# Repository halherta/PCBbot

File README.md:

# Introducing PCBbot!

The PCBBot leverages the PCB itself as the chassis. This reduces cost significantly. It also means that the two motors and the caster wheel would have to be mounted on the PCB itself, in addition to the batteries and all the other components...

For more info have a look at the write up on my [blog entry](https://hussamtalkstech.com/introducing-pcbbot/)

In this Github repo, you'll find my PCBBot KiCAD PCB design freely available (MIT License) along with a Digikey bill of materials (BOM) (caster wheel, motor brackets and motors not included) and MicroPython code. I’m also providing my [custom symbol and footprint libraries in this repo](https://github.com/halherta/mykicadlibrary). Feel free to make your own version of the PCBBot as is or modify it to suit your needs. Have fun!

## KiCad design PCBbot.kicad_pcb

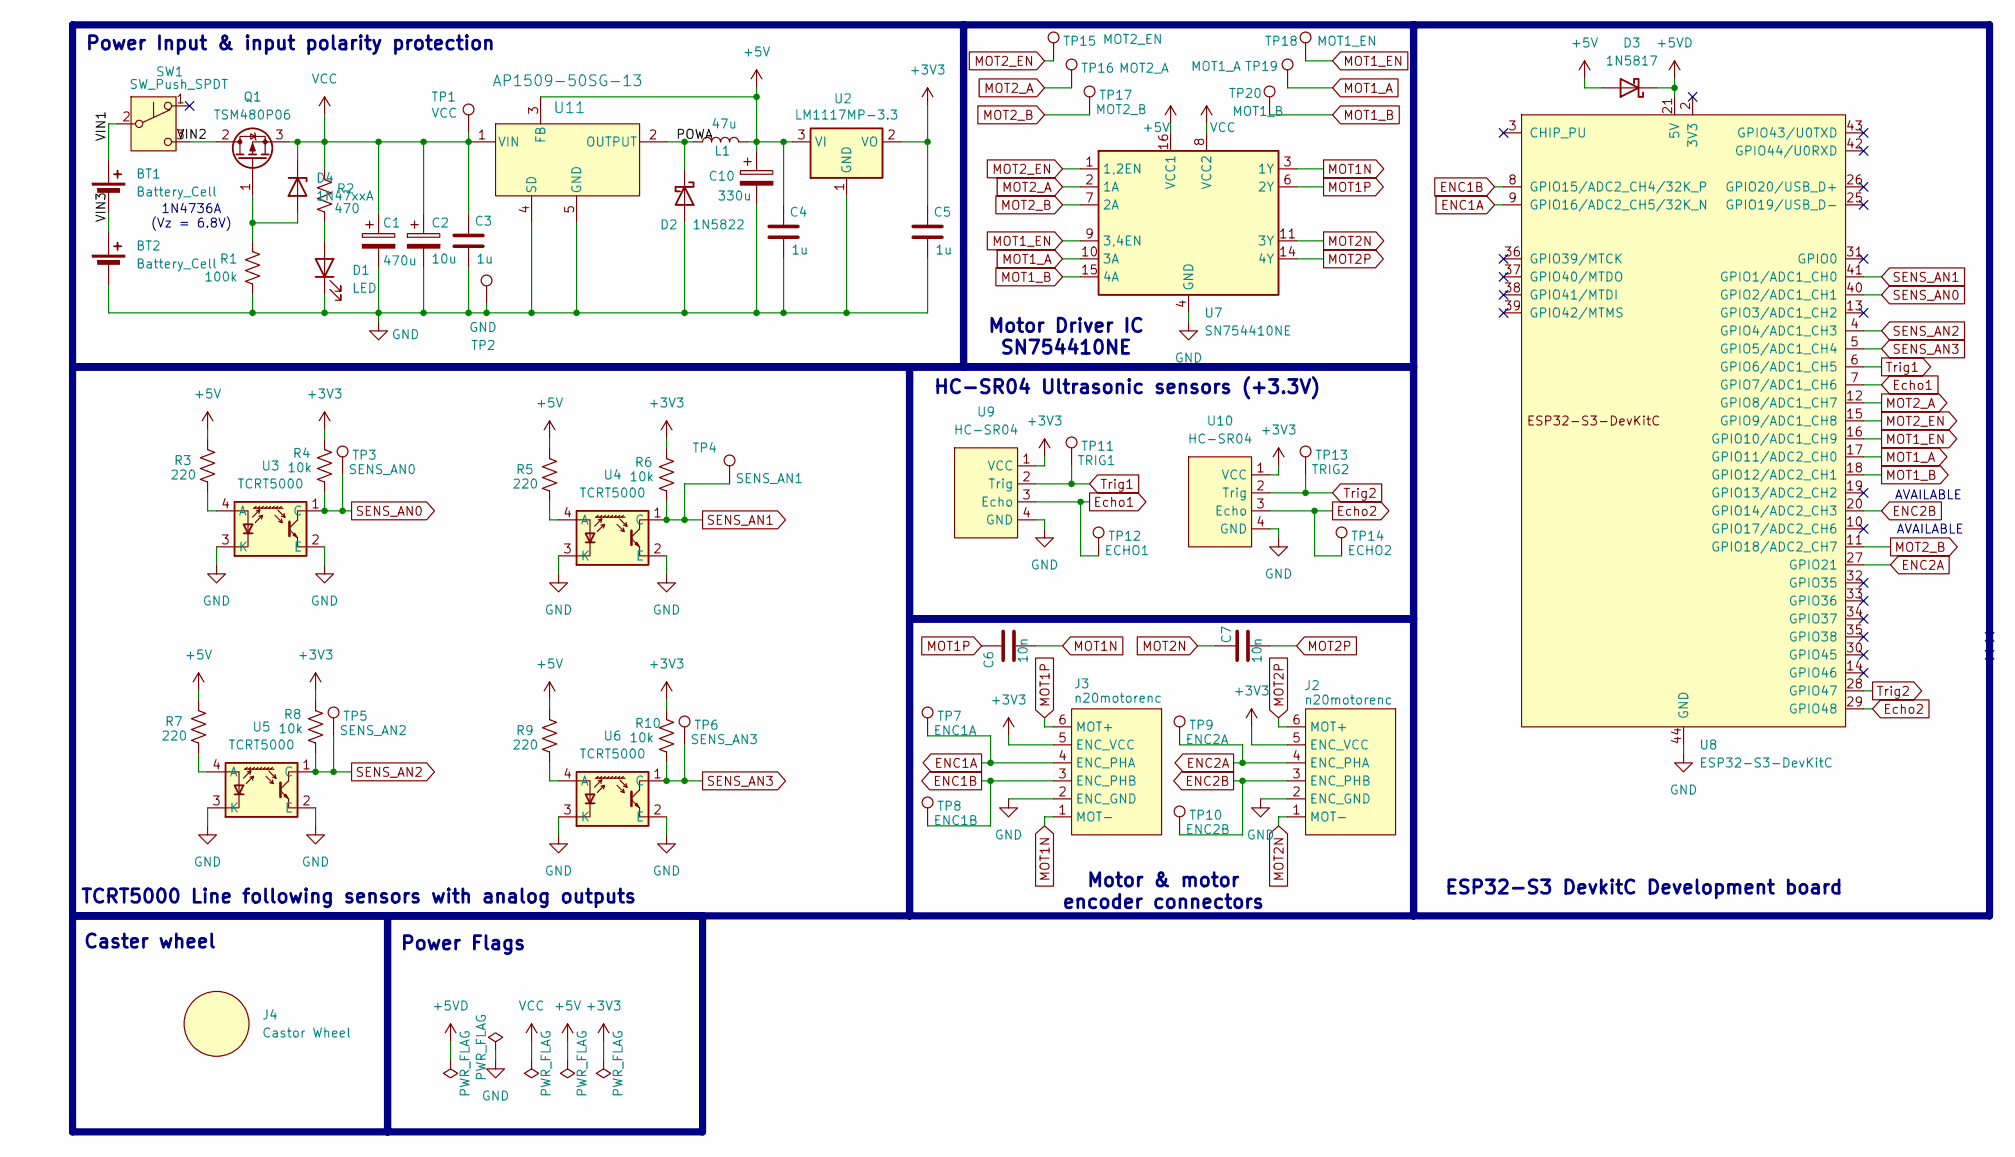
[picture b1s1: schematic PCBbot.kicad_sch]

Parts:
BT1, BT2: Battery_Cell; BatteryHolder_MPD_BK-18650-PC2
C1: 470u; CP_Radial_D10.0mm_P5.00mm
C2: 10u; CP_Radial_D5.0mm_P2.50mm
C3, C4, C5: 1u; C_Disc_D4.3mm_W1.9mm_P5.00mm
C6, C7: 10n; C_Disc_D4.3mm_W1.9mm_P5.00mm
C10: 330u; CP_Radial_D10.0mm_P5.00mm
D1: LED; LED_D5.0mm
D2: 1N5822; D_DO-201AD_P15.24mm_Horizontal
D3: 1N5817; D_DO-41_SOD81_P10.16mm_Horizontal
D4: 1N47xxA; D_DO-41_SOD81_P10.16mm_Horizontal
J2, J3: n20motorenc; n20motorencv2
J4: Castor Wheel; N20CasterSteelBall-Mini
L1: 47u; AIUR-06_ABRv2
Q1: TSM480P06; TO-251-3_Vertical
R1: 100k; R_Axial_DIN0207_L6.3mm_D2.5mm_P10.16mm_Horizontal
R2: 470; R_Axial_DIN0207_L6.3mm_D2.5mm_P10.16mm_Horizontal
R3, R5, R7, R9: 220; R_Axial_DIN0207_L6.3mm_D2.5mm_P10.16mm_Horizontal
R4, R6, R8, R10: 10k; R_Axial_DIN0207_L6.3mm_D2.5mm_P10.16mm_Horizontal
SW1: SW_Push_SPDT; SW_E-Switch_EG1224_SPDT_Angled
TP1: VCC; TestPoint_THTPad_D1.5mm_Drill0.7mm
TP2: GND; TestPoint_THTPad_D1.5mm_Drill0.7mm
TP3: SENS_AN0; TestPoint_THTPad_D1.5mm_Drill0.7mm
TP4: SENS_AN1; TestPoint_THTPad_D1.5mm_Drill0.7mm
TP5: SENS_AN2; TestPoint_THTPad_D1.5mm_Drill0.7mm
TP6: SENS_AN3; TestPoint_THTPad_D1.5mm_Drill0.7mm
TP7: ENC1A; TestPoint_THTPad_D1.5mm_Drill0.7mm
TP8: ENC1B; TestPoint_THTPad_D1.5mm_Drill0.7mm
TP9: ENC2A; TestPoint_THTPad_D1.5mm_Drill0.7mm
TP10: ENC2B; TestPoint_THTPad_D1.5mm_Drill0.7mm
TP11: TRIG1; TestPoint_THTPad_D1.5mm_Drill0.7mm
TP12: ECHO1; TestPoint_THTPad_D1.5mm_Drill0.7mm
TP13: TRIG2; TestPoint_THTPad_D1.5mm_Drill0.7mm
TP14: ECHO2; TestPoint_THTPad_D1.5mm_Drill0.7mm
TP15: MOT2_EN; TestPoint_THTPad_D1.5mm_Drill0.7mm
TP16: MOT2_A; TestPoint_THTPad_D1.5mm_Drill0.7mm
TP17: MOT2_B; TestPoint_THTPad_D1.5mm_Drill0.7mm
TP18: MOT1_EN; TestPoint_THTPad_D1.5mm_Drill0.7mm
TP19: MOT1_A; TestPoint_THTPad_D1.5mm_Drill0.7mm
TP20: MOT1_B; TestPoint_THTPad_D1.5mm_Drill0.7mm
U2: LM1117MP-3.3; SOT-223-3_TabPin2
U3, U4, U5, U6: TCRT5000; Vishay_TCRT5000
U7: SN754410NE; DIP-16_W7.62mm
U8: ESP32-S3-DevKitC
U9, U10: HC-SR04
U11: AP1509-50SG-13; SOP-8_3.9x4.9mm_P1.27mm

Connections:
+3V3: C5.1, J2.5 (ENC_VCC), J3.5 (ENC_VCC), R4.1, R6.1, R8.1, R10.1, U2.2 (VO), U9.1 (VCC), U10.1 (VCC)
+5V: C4.1, C10.1, D3.2 (A), L1.2, R3.1, R5.1, R7.1, R9.1, U2.3 (VI), U7.16 (VCC1), U11.3 (FB)
+5VD: D3.1 (K), U8.21 (5V)
/POWA: D2.1 (K), L1.1, U11.2 (OUTPUT)
/VIN1: BT1.1 (+), SW1.2 (B)
/VIN2: Q1.2 (D), SW1.3 (C)
/VIN3: BT1.2 (-), BT2.1 (+)
ENC1A: J3.4 (ENC_PHA), TP7.1, U8.9 (GPIO16/ADC2_CH5/32K_N)
ENC1B: J3.3 (ENC_PHB), TP8.1, U8.8 (GPIO15/ADC2_CH4/32K_P)
ENC2A: J2.4 (ENC_PHA), TP9.1, U8.27 (GPIO21)
ENC2B: J2.3 (ENC_PHB), TP10.1, U8.20 (GPIO14/ADC2_CH3)
Echo1: TP12.1, U8.7 (GPIO7/ADC1_CH6), U9.3 (Echo)
Echo2: TP14.1, U8.29 (GPIO48), U10.3 (Echo)
GND: BT2.2 (-), C1.2, C2.2, C3.2, C4.2, C5.2, C10.2, D1.1 (K), D2.2 (A), J2.2 (ENC_GND), J3.2 (ENC_GND), R1.2, TP2.1, U2.1 (GND), U3.2 (E), U3.3 (K), U4.2 (E), U4.3 (K), U5.2 (E), U5.3 (K), U6.2 (E), U6.3 (K), U7.4 (GND), U7.5 (GND), U7.12 (GND), U7.13 (GND), U8.22 (GND), U8.23 (GND), U8.24 (GND), U8.44 (GND), U9.4 (GND), U10.4 (GND), U11.4 (SD), U11.5 (GND), U11.6 (GND), U11.7 (GND), U11.8 (GND)
MOT1N: C6.2, J3.1 (MOT-), U7.3 (1Y)
MOT1P: C6.1, J3.6 (MOT+), U7.6 (2Y)
MOT1_A: TP19.1, U7.10 (3A), U8.17 (GPIO11/ADC2_CH0)
MOT1_B: TP20.1, U7.15 (4A), U8.18 (GPIO12/ADC2_CH1)
MOT1_EN: TP18.1, U7.9 (3,4EN), U8.16 (GPIO10/ADC1_CH9)
MOT2N: C7.1, J2.1 (MOT-), U7.11 (3Y)
MOT2P: C7.2, J2.6 (MOT+), U7.14 (4Y)
MOT2_A: TP16.1, U7.2 (1A), U8.12 (GPIO8/ADC1_CH7)
MOT2_B: TP17.1, U7.7 (2A), U8.11 (GPIO18/ADC2_CH7)
MOT2_EN: TP15.1, U7.1 (1,2EN), U8.15 (GPIO9/ADC1_CH8)
unnamed: D1.2 (A), R2.2
unnamed: D4.2 (A), Q1.1 (G), R1.1
unnamed: R3.2, U3.4 (A)
unnamed: R5.2, U4.4 (A)
unnamed: R7.2, U5.4 (A)
unnamed: R9.2, U6.4 (A)
SENS_AN0: R4.2, TP3.1, U3.1 (C), U8.40 (GPIO2/ADC1_CH1)
SENS_AN1: R6.2, TP4.1, U4.1 (C), U8.41 (GPIO1/ADC1_CH0)
SENS_AN2: R8.2, TP5.1, U5.1 (C), U8.4 (GPIO4/ADC1_CH3)
SENS_AN3: R10.2, TP6.1, U6.1 (C), U8.5 (GPIO5/ADC1_CH4)
Trig1: TP11.1, U8.6 (GPIO6/ADC1_CH5), U9.2 (Trig)
Trig2: TP13.1, U8.28 (GPIO47), U10.2 (Trig)
VCC: C1.1, C2.1, C3.1, D4.1 (K), Q1.3 (S), R2.1, TP1.1, U7.8 (VCC2), U11.1 (VIN)

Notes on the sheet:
HC-SR04 Ultrasonic sensors (+3.3V)
Power Input & input polarity protection
Motor Driver IC SN754410NE
Motor & motor encoder connectors
AVAILABLE
Caster wheel
1N4736A (Vz = 6.8V)
ESP32-S3 DevkitC Development board
TCRT5000 Line following sensors with analog outputs
Power Flags

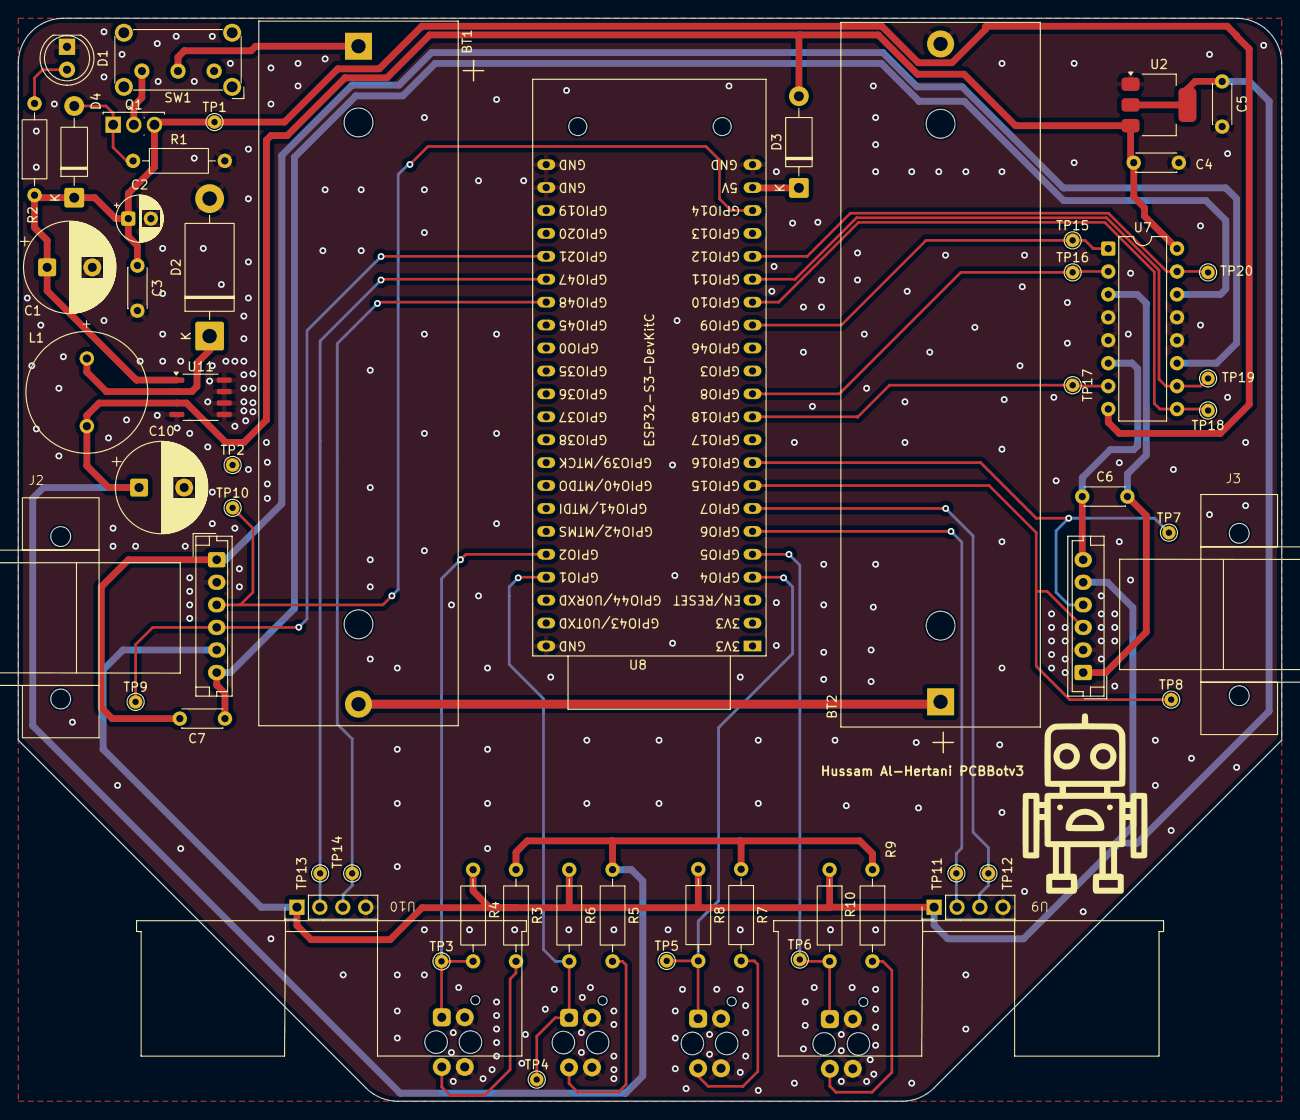
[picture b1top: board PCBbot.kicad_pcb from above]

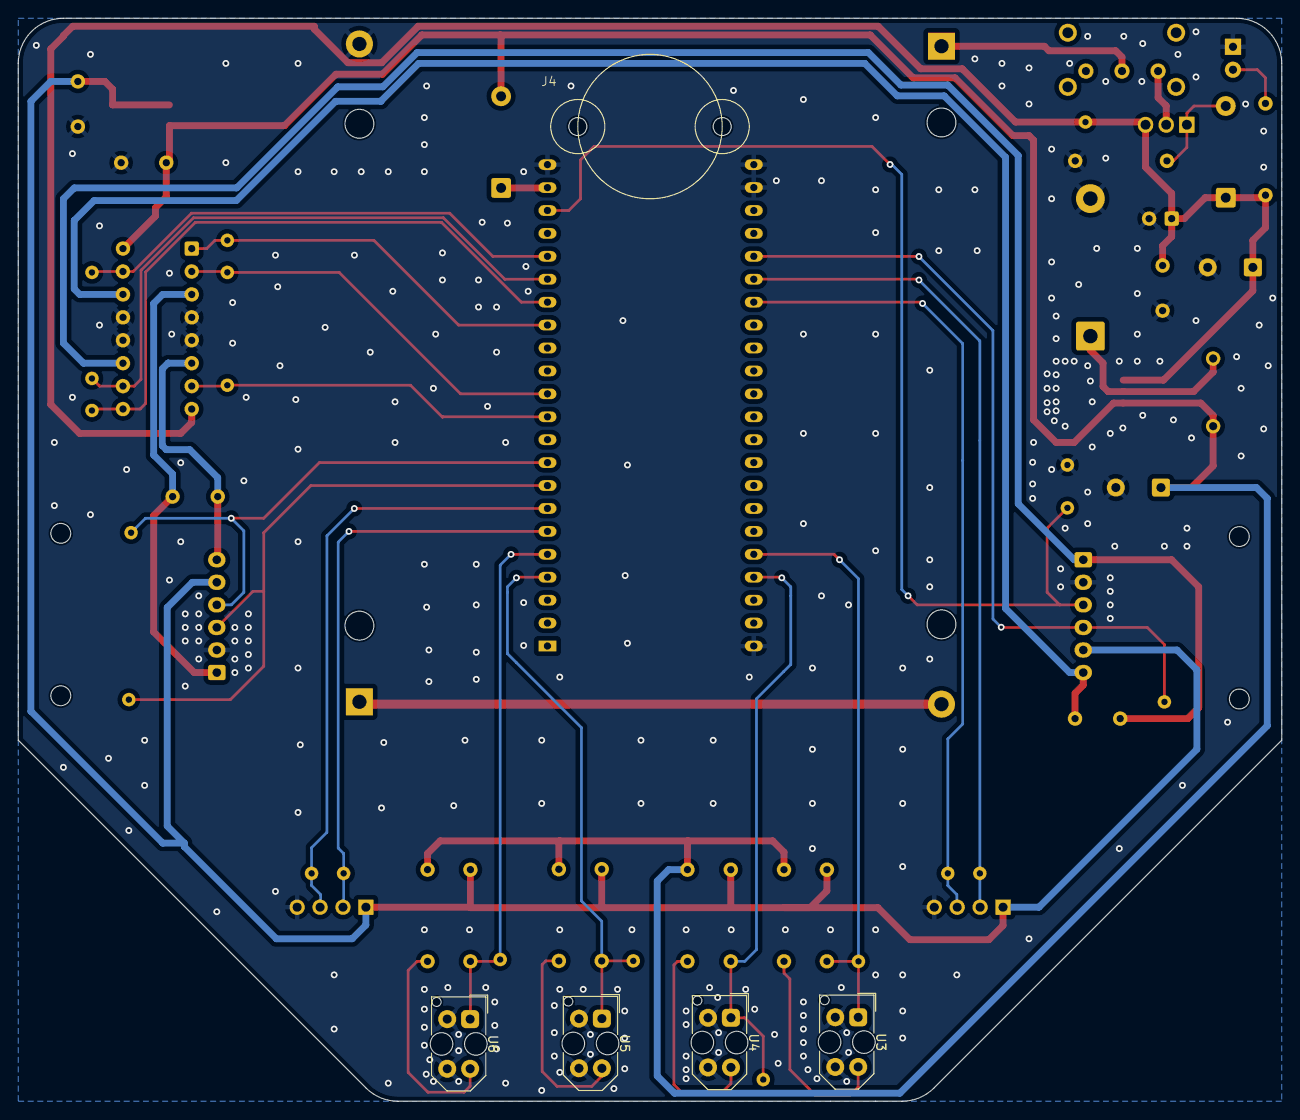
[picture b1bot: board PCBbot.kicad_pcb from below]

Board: 2 copper layers, 140.0 x 120.0 mm, 60 parts (5 on the bottom side), 37 nets.

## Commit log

2025-07-29 added digikey bom
2025-08-18 added sample micropython code
2025-08-18 commented code and cleaned up a bit
2025-08-24 Added a LICENSE file (MIT License)
2025-08-24 Update README.md
    updated README.md
